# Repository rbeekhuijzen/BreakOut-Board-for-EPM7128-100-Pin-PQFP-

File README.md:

# BreakOut-Board-for-EPM7128-100-Pin-PQFP-
A break out board for the EPM7128x in a 100 pin PQFP.

Made with KiCAD 8.0.x.

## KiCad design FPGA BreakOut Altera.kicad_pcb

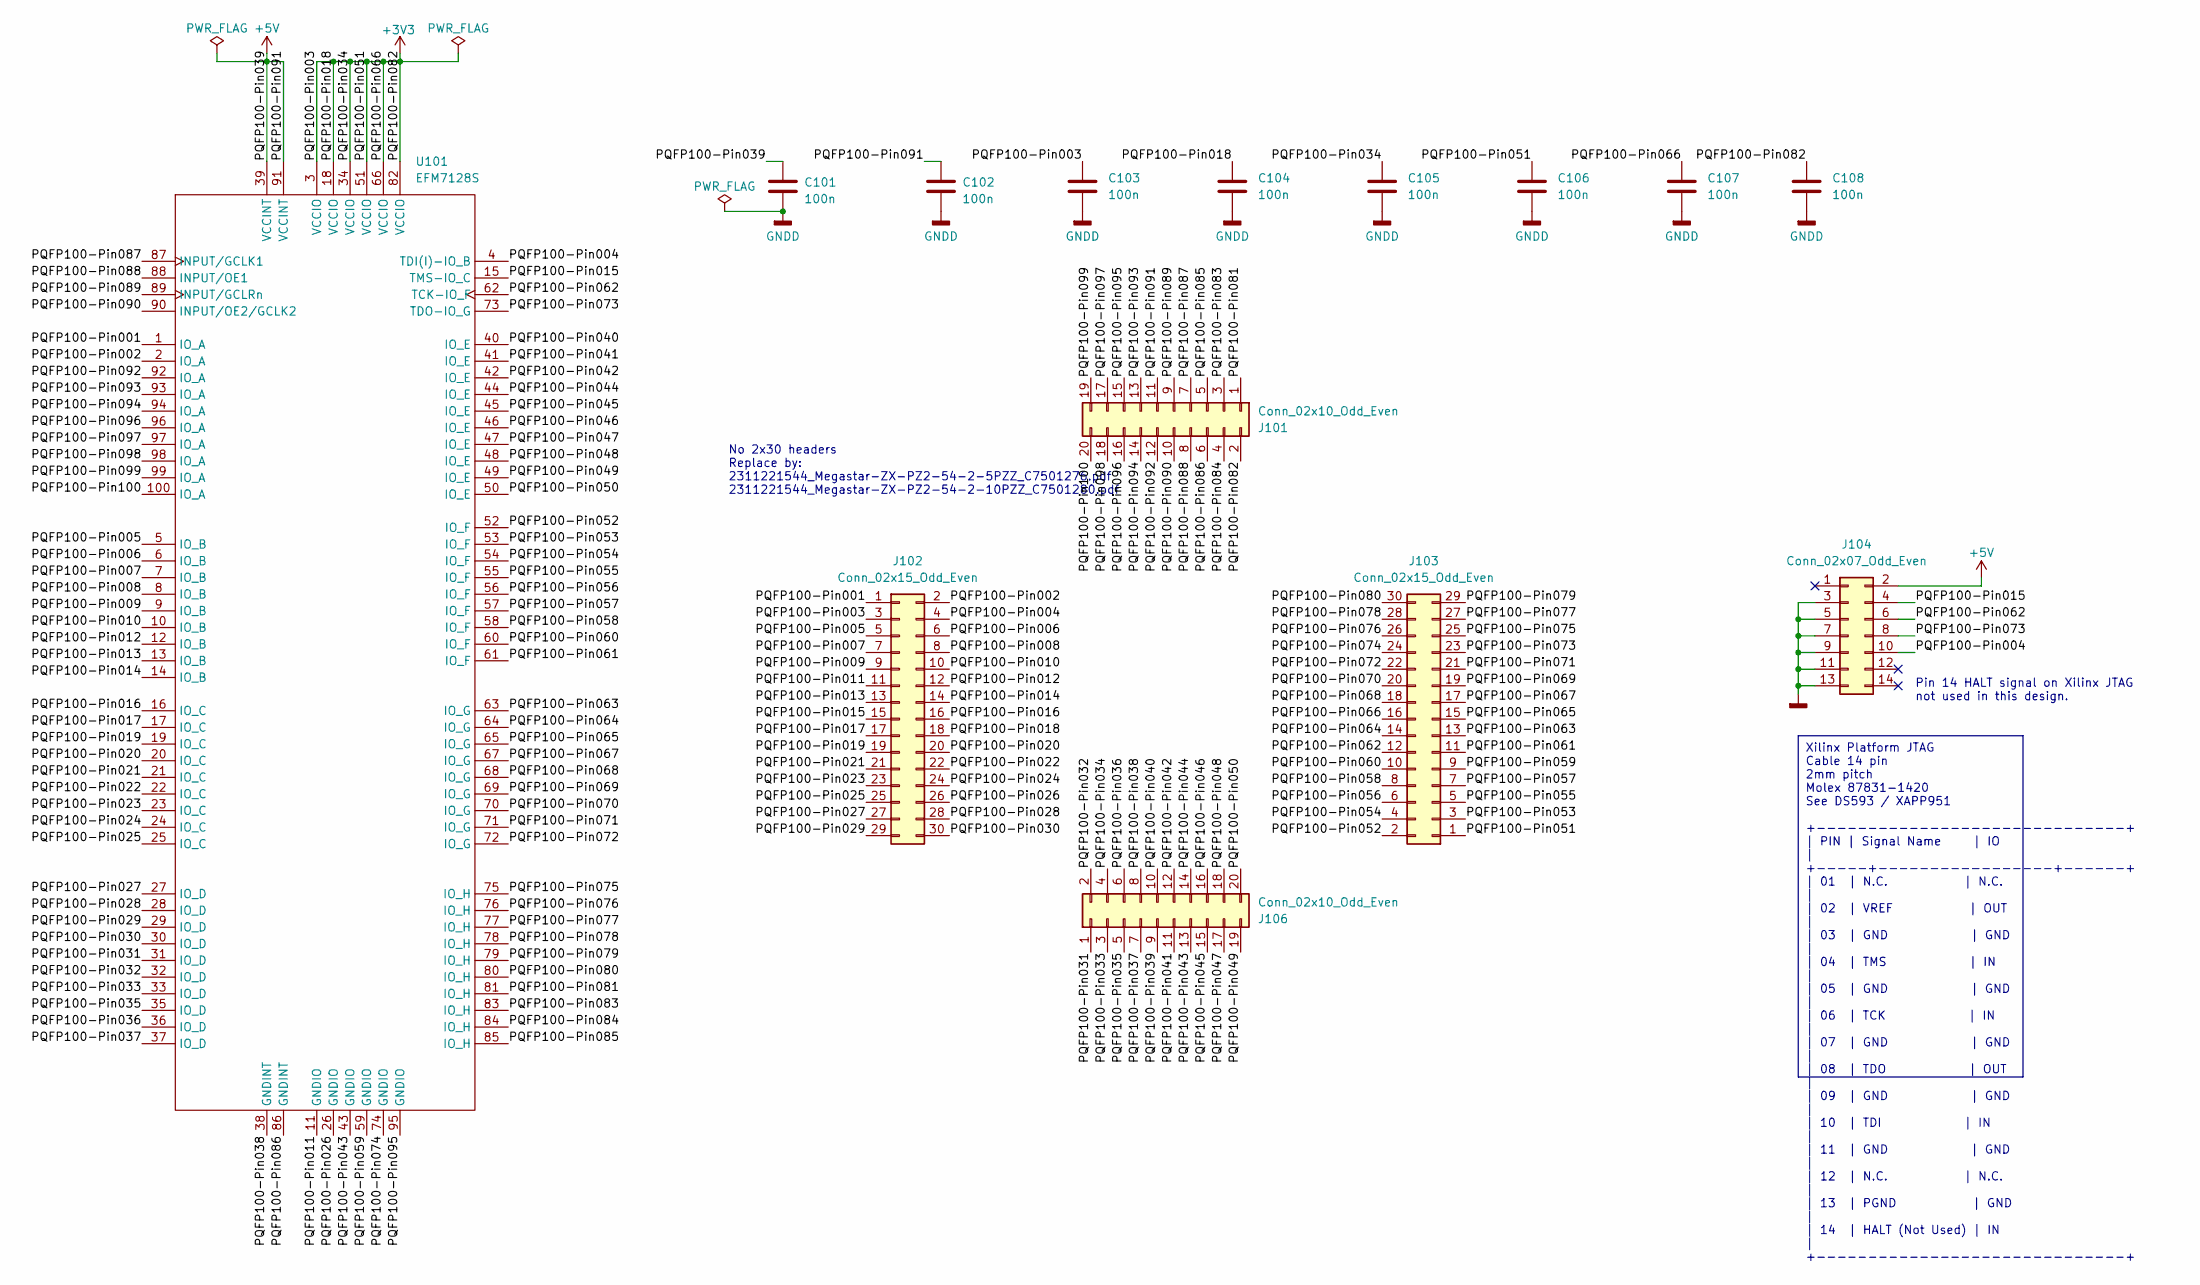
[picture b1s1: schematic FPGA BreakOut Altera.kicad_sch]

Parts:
C101, C102, C103, C104, C105, C106, C107, C108: 100n; C_0603_1608Metric_Pad1.08x0.95mm_HandSolder; Partnumber Manufacturer CC0603MRY5V8BB104; LCSC Part # C519502
J101, J106: Conn_02x10_Odd_Even; PinHeader_2x10_P2.54mm_Vertical; JLCPCB Part Number C7501280
J102, J103: Conn_02x15_Odd_Even; PinHeader_2x15_P2.54mm_Vertical
J104: Conn_02x07_Odd_Even; PinSocket_2x07_P2.00mm_Vertical; Partnumber Manufacturer 878311420; LCSC Part # C240854
U101: EFM7128S; PQFP-100_14x20mm_P0.65mm

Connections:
+3V3: C103.1, C104.1, C105.1, C106.1, C107.1, C108.1, J101.2, J102.3, J102.18, J103.1, J103.16, J106.4, U101.3 (VCCIO), U101.18 (VCCIO), U101.34 (VCCIO), U101.51 (VCCIO), U101.66 (VCCIO), U101.82 (VCCIO)
+5V: C101.1, C102.1, J101.11, J104.2, J106.9, U101.39 (VCCINT), U101.91 (VCCINT)
/PQFP100-Pin001: J102.1, U101.1 (IO_A)
/PQFP100-Pin002: J102.2, U101.2 (IO_A)
/PQFP100-Pin004: J102.4, J104.10, U101.4 (TDI(I)-IO_B)
/PQFP100-Pin005: J102.5, U101.5 (IO_B)
/PQFP100-Pin006: J102.6, U101.6 (IO_B)
/PQFP100-Pin007: J102.7, U101.7 (IO_B)
/PQFP100-Pin008: J102.8, U101.8 (IO_B)
/PQFP100-Pin009: J102.9, U101.9 (IO_B)
/PQFP100-Pin010: J102.10, U101.10 (IO_B)
/PQFP100-Pin011: J102.11, U101.11 (GNDIO)
/PQFP100-Pin012: J102.12, U101.12 (IO_B)
/PQFP100-Pin013: J102.13, U101.13 (IO_B)
/PQFP100-Pin014: J102.14, U101.14 (IO_B)
/PQFP100-Pin015: J102.15, J104.4, U101.15 (TMS-IO_C)
/PQFP100-Pin016: J102.16, U101.16 (IO_C)
/PQFP100-Pin017: J102.17, U101.17 (IO_C)
/PQFP100-Pin019: J102.19, U101.19 (IO_C)
/PQFP100-Pin020: J102.20, U101.20 (IO_C)
/PQFP100-Pin021: J102.21, U101.21 (IO_C)
/PQFP100-Pin022: J102.22, U101.22 (IO_C)
/PQFP100-Pin023: J102.23, U101.23 (IO_C)
/PQFP100-Pin024: J102.24, U101.24 (IO_C)
/PQFP100-Pin025: J102.25, U101.25 (IO_C)
/PQFP100-Pin026: J102.26, U101.26 (GNDIO)
/PQFP100-Pin027: J102.27, U101.27 (IO_D)
/PQFP100-Pin028: J102.28, U101.28 (IO_D)
/PQFP100-Pin029: J102.29, U101.29 (IO_D)
/PQFP100-Pin030: J102.30, U101.30 (IO_D)
/PQFP100-Pin031: J106.1, U101.31 (IO_D)
/PQFP100-Pin032: J106.2, U101.32 (IO_D)
/PQFP100-Pin033: J106.3, U101.33 (IO_D)
/PQFP100-Pin035: J106.5, U101.35 (IO_D)
/PQFP100-Pin036: J106.6, U101.36 (IO_D)
/PQFP100-Pin037: J106.7, U101.37 (IO_D)
/PQFP100-Pin038: J106.8, U101.38 (GNDINT)
/PQFP100-Pin040: J106.10, U101.40 (IO_E)
/PQFP100-Pin041: J106.11, U101.41 (IO_E)
/PQFP100-Pin042: J106.12, U101.42 (IO_E)
/PQFP100-Pin043: J106.13, U101.43 (GNDIO)
/PQFP100-Pin044: J106.14, U101.44 (IO_E)
/PQFP100-Pin045: J106.15, U101.45 (IO_E)
/PQFP100-Pin046: J106.16, U101.46 (IO_E)
/PQFP100-Pin047: J106.17, U101.47 (IO_E)
/PQFP100-Pin048: J106.18, U101.48 (IO_E)
/PQFP100-Pin049: J106.19, U101.49 (IO_E)
/PQFP100-Pin050: J106.20, U101.50 (IO_E)
/PQFP100-Pin052: J103.2, U101.52 (IO_F)
/PQFP100-Pin053: J103.3, U101.53 (IO_F)
/PQFP100-Pin054: J103.4, U101.54 (IO_F)
/PQFP100-Pin055: J103.5, U101.55 (IO_F)
/PQFP100-Pin056: J103.6, U101.56 (IO_F)
/PQFP100-Pin057: J103.7, U101.57 (IO_F)
/PQFP100-Pin058: J103.8, U101.58 (IO_F)
/PQFP100-Pin059: J103.9, U101.59 (GNDIO)
/PQFP100-Pin060: J103.10, U101.60 (IO_F)
/PQFP100-Pin061: J103.11, U101.61 (IO_F)
/PQFP100-Pin062: J103.12, J104.6, U101.62 (TCK-IO_F)
/PQFP100-Pin063: J103.13, U101.63 (IO_G)
/PQFP100-Pin064: J103.14, U101.64 (IO_G)
/PQFP100-Pin065: J103.15, U101.65 (IO_G)
/PQFP100-Pin067: J103.17, U101.67 (IO_G)
/PQFP100-Pin068: J103.18, U101.68 (IO_G)
/PQFP100-Pin069: J103.19, U101.69 (IO_G)
/PQFP100-Pin070: J103.20, U101.70 (IO_G)
/PQFP100-Pin071: J103.21, U101.71 (IO_G)
/PQFP100-Pin072: J103.22, U101.72 (IO_G)
/PQFP100-Pin073: J103.23, J104.8, U101.73 (TDO-IO_G)
/PQFP100-Pin074: J103.24, U101.74 (GNDIO)
/PQFP100-Pin075: J103.25, U101.75 (IO_H)
/PQFP100-Pin076: J103.26, U101.76 (IO_H)
/PQFP100-Pin077: J103.27, U101.77 (IO_H)
/PQFP100-Pin078: J103.28, U101.78 (IO_H)
/PQFP100-Pin079: J103.29, U101.79 (IO_H)
/PQFP100-Pin080: J103.30, U101.80 (IO_H)
/PQFP100-Pin081: J101.1, U101.81 (IO_H)
/PQFP100-Pin083: J101.3, U101.83 (IO_H)
/PQFP100-Pin084: J101.4, U101.84 (IO_H)
/PQFP100-Pin085: J101.5, U101.85 (IO_H)
/PQFP100-Pin086: J101.6, U101.86 (GNDINT)
/PQFP100-Pin087: J101.7, U101.87 (INPUT/GCLK1)
/PQFP100-Pin088: J101.8, U101.88 (INPUT/OE1)
/PQFP100-Pin089: J101.9, U101.89 (INPUT/GCLRn)
/PQFP100-Pin090: J101.10, U101.90 (INPUT/OE2/GCLK2)
/PQFP100-Pin092: J101.12, U101.92 (IO_A)
/PQFP100-Pin093: J101.13, U101.93 (IO_A)
/PQFP100-Pin094: J101.14, U101.94 (IO_A)
/PQFP100-Pin095: J101.15, U101.95 (GNDIO)
/PQFP100-Pin096: J101.16, U101.96 (IO_A)
/PQFP100-Pin097: J101.17, U101.97 (IO_A)
/PQFP100-Pin098: J101.18, U101.98 (IO_A)
/PQFP100-Pin099: J101.19, U101.99 (IO_A)
/PQFP100-Pin100: J101.20, U101.100 (IO_A)
GNDD: C101.2, C102.2, C103.2, C104.2, C105.2, C106.2, C107.2, C108.2, J104.3, J104.5, J104.7, J104.9, J104.11, J104.13

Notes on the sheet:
Xilinx Platform JTAG Cable 14 pin 2mm pitch Molex 87831-1420 See DS593 / XAPP951 +------------------------------+ | PIN | Signal Name | IO | +-----+-----------------+------+ | 01 | N.C. | N.C. | | 02 | VREF | OUT | | 03 | GND | GND | | 04 | TMS | IN | | 05 | GND | GND | | 06 | TCK | IN | | 07 | GND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
No 2x30 headers Replace by: 2311221544_Megastar-ZX-PZ2-54-2-5PZZ_C7501276.pdf 2311221544_Megastar-ZX-PZ2-54-2-10PZZ_C7501280.pdf
Pin 14 HALT signal on Xilinx JTAG not used in this design.

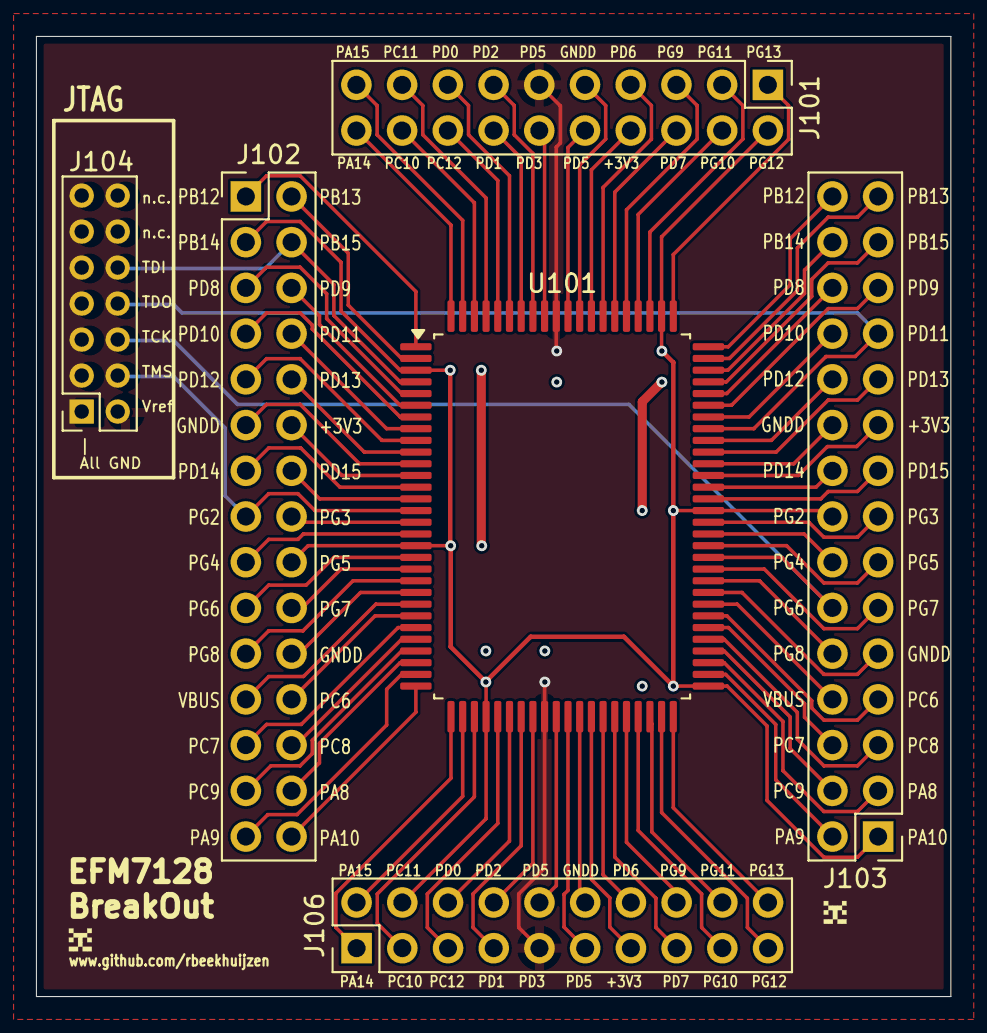
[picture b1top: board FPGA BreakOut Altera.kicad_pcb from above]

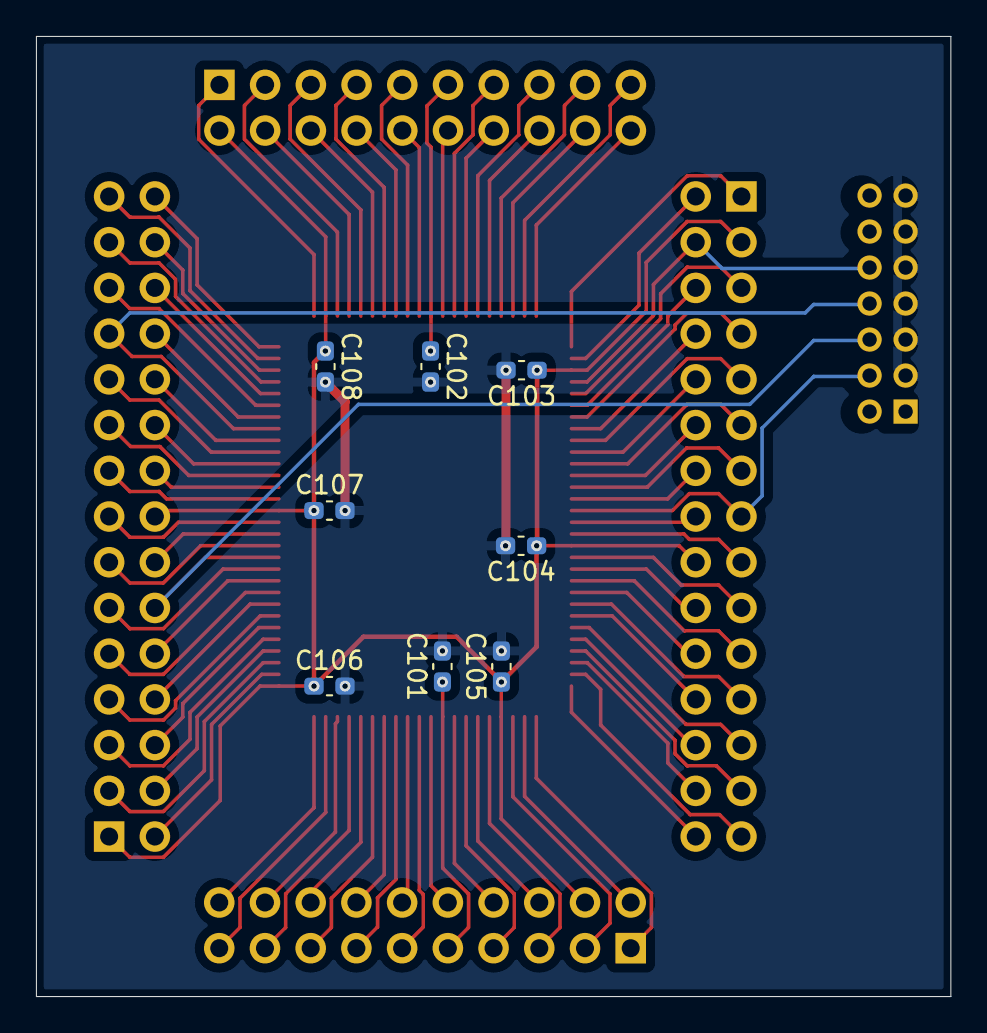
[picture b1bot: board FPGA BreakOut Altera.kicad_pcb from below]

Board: 2 copper layers, 50.8 x 53.3 mm, 14 parts (8 on the bottom side), 95 nets.
